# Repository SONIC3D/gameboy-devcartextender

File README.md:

# Gameboy Development Cart Extender
## Introduction
This is a gameboy game cartridge extenter board. Used for expose debug pins for connecting external logic analyzer.

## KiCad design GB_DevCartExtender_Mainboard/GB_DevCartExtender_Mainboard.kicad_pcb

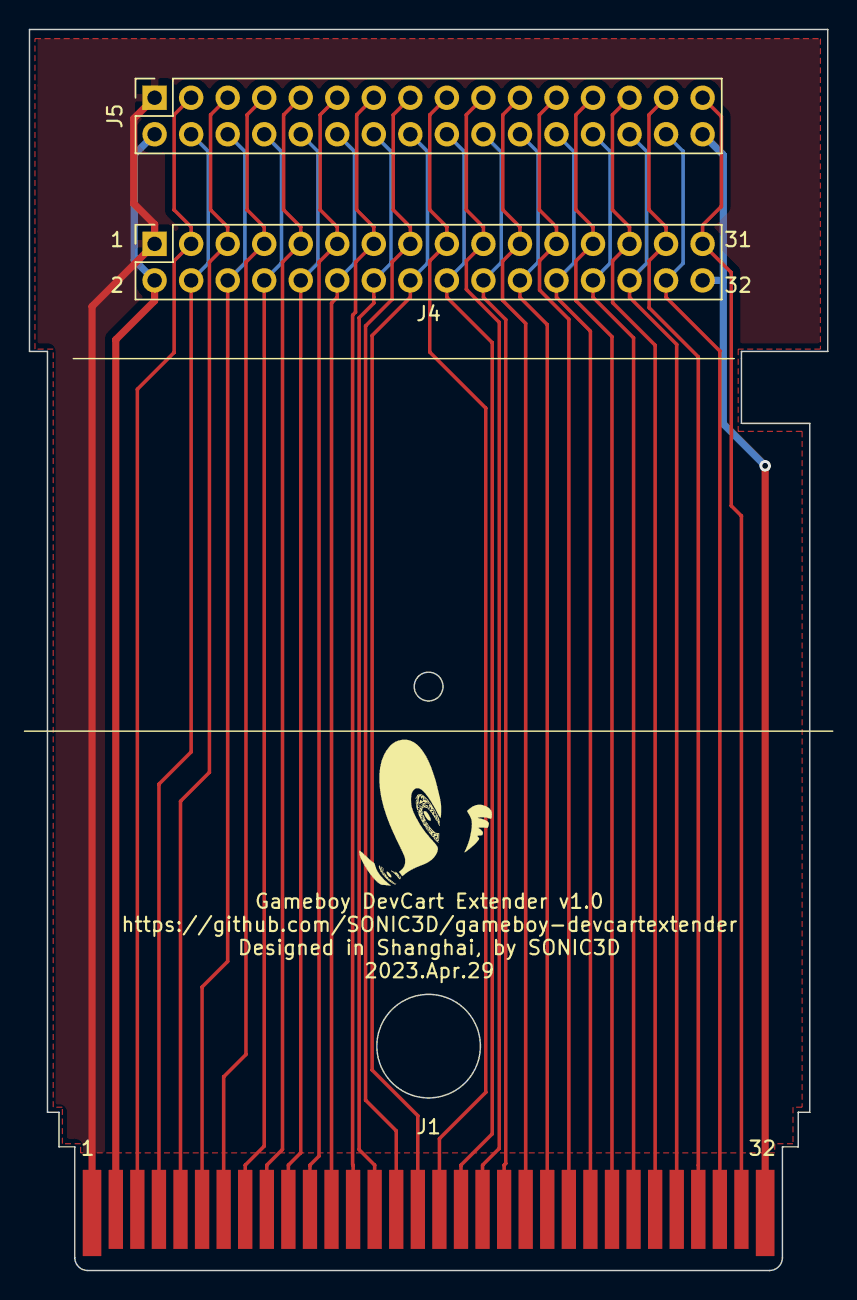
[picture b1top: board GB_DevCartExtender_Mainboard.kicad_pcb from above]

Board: 2 copper layers, 55.5 x 86.3 mm, 3 parts (0 on the bottom side), 32 nets.

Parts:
J1: GB_Cart_EdgeConn-1Row-32Pins; GB_Cart_1x32_P1.50mm_Edge_For_CartShell
J4, J5: Conn_02x16_Odd_Even; PinSocket_2x16_P2.54mm_Vertical

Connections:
+5V: J1.1, J4.1, J5.1
/AA0: J1.6, J4.6, J5.6
/AA1: J1.7, J4.7, J5.7
/AA2: J1.8, J4.8, J5.8
/AA3: J1.9, J4.9, J5.9
/AA4: J1.10, J4.10, J5.10
/AA5: J1.11, J4.11, J5.11
/AA6: J1.12, J4.12, J5.12
/AA7: J1.13, J4.13, J5.13
/AA8: J1.14, J4.14, J5.14
/AA9: J1.15, J4.15, J5.15
/AA10: J1.16, J4.16, J5.16
/AA11: J1.17, J4.17, J5.17
/AA12: J1.18, J4.18, J5.18
/AA13: J1.19, J4.19, J5.19
/AA14: J1.20, J4.20, J5.20
/AA15: J1.21, J4.21, J5.21
/AAudioIn: J1.31, J4.31, J5.31
/ACLK: J1.2, J4.2, J5.2
/AD0: J1.22, J4.22, J5.22
/AD1: J1.23, J4.23, J5.23
/AD2: J1.24, J4.24, J5.24
/AD3: J1.25, J4.25, J5.25
/AD4: J1.26, J4.26, J5.26
/AD5: J1.27, J4.27, J5.27
/AD6: J1.28, J4.28, J5.28
/AD7: J1.29, J4.29, J5.29
/~ARD: J1.4, J4.4, J5.4
/~ARST: J1.30, J4.30, J5.30
/~ASRAM_CS: J1.5, J4.5, J5.5
/~AWR: J1.3, J4.3, J5.3
GND: J1.32, J4.32, J5.32

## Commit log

2023-04-29 Added: README file.
2023-04-29 Added: Required 3rd party repository of symbols and footprints.
2023-04-29 Added: Git ignore rules.
2023-04-29 Added: Mainboard project.(Tracks are not yet routed.)
2023-04-29 Modified: PCB routed.
2023-04-29 Modified: Filled zone added.
2023-04-29 Modified: Logo added.
2023-04-29 Added: Gerber files for v1.0 mainboard.
2023-04-29 Modified: Modified filled zone on back side.
2023-04-29 Modified: Gerber files regenerated.
